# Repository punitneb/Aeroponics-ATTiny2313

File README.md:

# Aeroponics-ATTiny2313
This project is specifically tailored to components available in the Indian market, keeping in mind rural farm practices and conditions. At the same time attempting to keep the design suitable for urban farming.

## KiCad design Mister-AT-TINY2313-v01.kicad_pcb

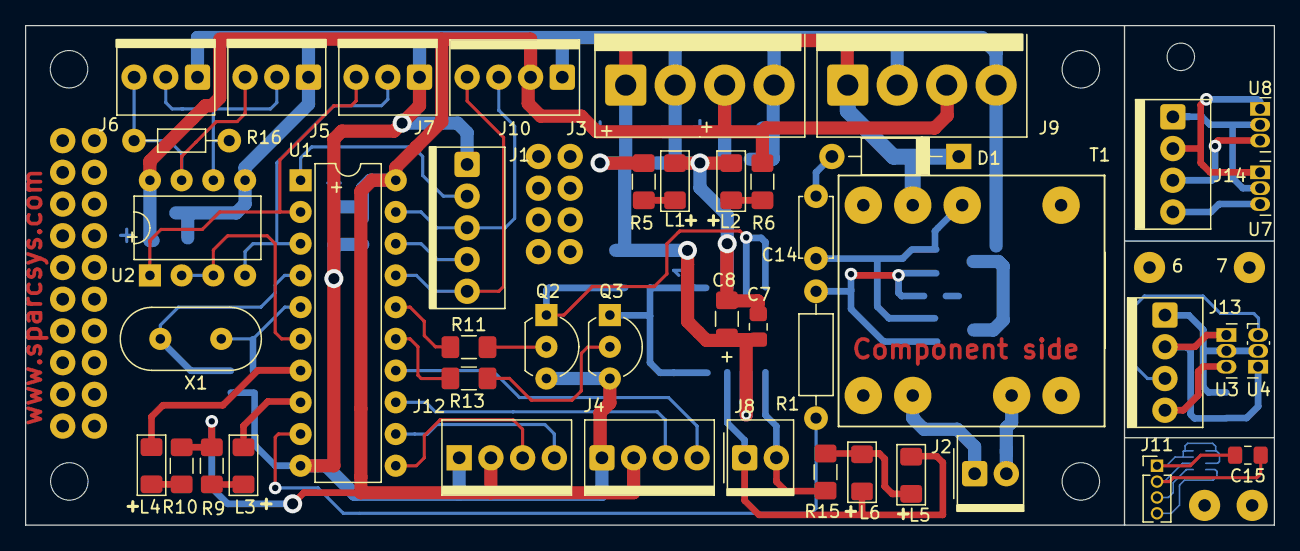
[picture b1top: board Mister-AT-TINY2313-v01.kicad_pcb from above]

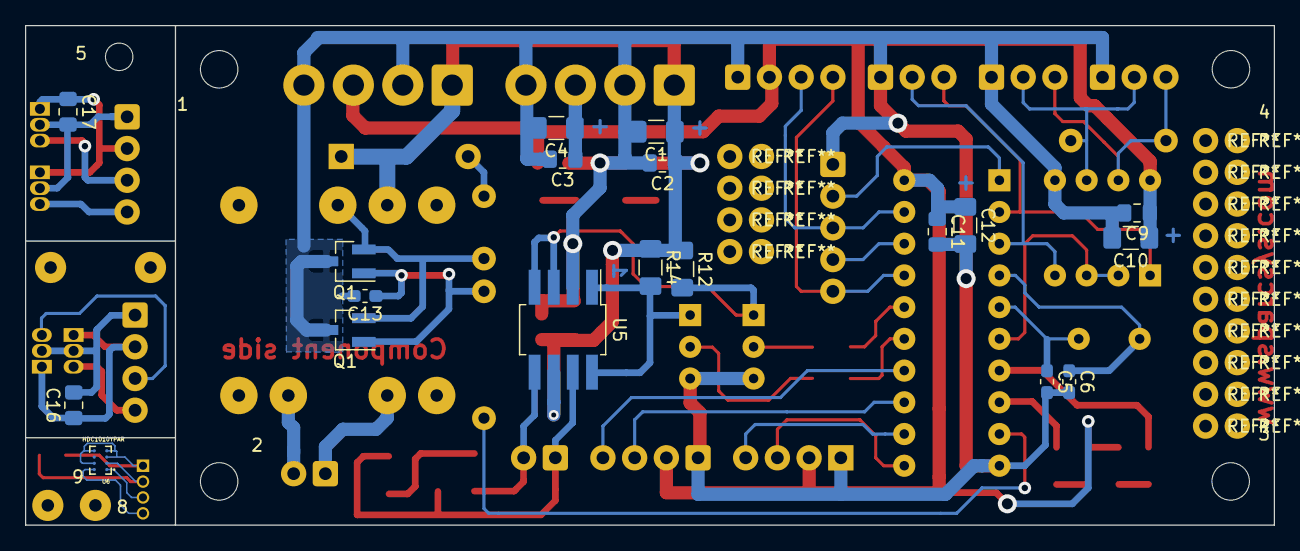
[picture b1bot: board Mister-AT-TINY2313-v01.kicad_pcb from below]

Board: 2 copper layers, 100.0 x 40.0 mm, 72 parts (19 on the bottom side), 51 nets.

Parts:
1, 2, 3, 4: MountingHole_3mm
5: MountingHole_2.2mm_M2
6, 7, 8, 9: SolderWirePad_1x01_Drill1mm
C1, C4, C8, C10, C12: 100uf/16V; C_1206_3216Metric_Pad1.42x1.75mm_HandSolder
C2, C3, C7, C9, C11: 104; C_0805_2012Metric_Pad1.15x1.40mm_HandSolder
C5, C6, C13: 22pf; C_0603_1608Metric_Pad1.05x0.95mm_HandSolder
C14: 0.22/100V; C_Disc_D4.7mm_W2.5mm_P5.00mm
C15, C16, C17: 104; R_0805_2012Metric_Pad1.15x1.40mm_HandSolder
D1: 1N4001; D_DO-41_SOD81_P10.16mm_Horizontal
J1: 5P RELI M; Molex_KK-254_AE-6410-05A_1x05_P2.54mm_Vertical
J2, J8: 2P RELI M; Molex_KK-254_AE-6410-02A_1x02_P2.54mm_Vertical
J3, J9: 4P CPU M; Hirose_DF63-4P-3.96DSA_1x04_P3.96mm_Horizontal
J4, J10, J12, J13, J14: 4P RELI M; Molex_KK-254_AE-6410-04A_1x04_P2.54mm_Vertical
J5, J6, J7: 3P RELI M; Molex_KK-254_AE-6410-03A_1x03_P2.54mm_Vertical
J11: 4P RELI M; PinHeader_1x04_P1.27mm_Vertical
L1: Green; LED_1206_3216Metric_Pad1.42x1.75mm_HandSolder
L2: Red; LED_1206_3216Metric_Pad1.42x1.75mm_HandSolder
L3: Blue; LED_1206_3216Metric_Pad1.42x1.75mm_HandSolder
L4: White; LED_1206_3216Metric_Pad1.42x1.75mm_HandSolder
L5: RED; LED_1206_3216Metric_Pad1.42x1.75mm_HandSolder
L6: BLUE; LED_1206_3216Metric_Pad1.42x1.75mm_HandSolder
Q1, Q1#2: TIP122; SOT-23_Handsoldering
Q2, Q3: BC547; TO-92L_Inline_Wide
R1: 10K; R_Axial_DIN0207_L6.3mm_D2.5mm_P10.16mm_Horizontal
R5, R6, R11, R12, R13, R14: 4K7; R_1206_3216Metric_Pad1.42x1.75mm_HandSolder
R9, R10, R15: 2K2; R_1206_3216Metric_Pad1.42x1.75mm_HandSolder
R16: 100E; R_Axial_DIN0204_L3.6mm_D1.6mm_P7.62mm_Horizontal
T1: Transformer-20x20-3.96mm-10p
U1: ATtiny2313-20PU; DIP-20_W7.62mm
U2: MAX485E; DIP-8_W7.62mm_Socket_LongPads
U3, U4, U7, U8: A1343; Allegro_SIP-3
U5: ZXMHC6A07T8-H-Bridge-FET; SOT-223-8
U6: HDC1010YPAR; BGA8C100X50P2X4_204X159X67N
X1: 11.0592MHz; Crystal_HC49-U_Vertical

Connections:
+5V: C3.1, C4.1, C9.1, C10.1, C11.1, C12.1, J3.3, J4.2, J9.3, J10.2, J12.2, R6.1, R9.1, R10.1, U1.20, U2.8
+12V: C1.1, C2.1, C7.1, C8.1, D1.1, J3.1, J9.1, R5.1, R12.1, R14.1, T1.4, U5.6
/GND_H20: C17.2, J14.1, U7.2, U8.2
/GND_HALL_VALVE: C16.2, J13.1, U3.2, U4.2
/GND_HUSENS: C15.2, J11.1, U6.B2, U6.C1, U6.D1, U6.D2
/HALL_H2O_LVL1: J14.3, U8.3
/HALL_H2O_LVL2: J14.4, U7.3
/HALL_VALVE_CLOSE: J13.4, U3.3
/HALL_VALVE_OPEN: J13.3, U4.3
/L1_Anode: L1.2, R5.2
/L2_Anode: L2.2, R6.2
/MISO: J1.4, U1.18
/MOSI: J1.5, J10.4, U1.17
/MOTOR+: J8.2, R15.1, U5.5
/MOTOR-: J8.1, L5.1, L6.2, U5.7
/MOTOR_LED: L5.2, L6.1, R15.2
/PIEZO1: J2.1, T1.7
/PIEZO2: J2.2, T1.8
/PORT_HALL_H2O_LVL1: J12.3, U1.11
/PORT_HALL_H2O_LVL2: J12.4, U1.12
/PORT_HALL_VALVE_CLOSE: J4.4, U1.14
/PORT_HALL_VALVE_OPEN: J4.3, U1.13
/PORT_LED_ACTIVITY: L4.1, U1.7
/PORT_LED_LOOP: L3.1, U1.8
/PORT_MOTOR_F: R11.2, U1.16
/PORT_MOTOR_R: R13.2, U1.15
/PORT_PWM: R1.2, U1.9
/PORT_RX: J7.3, U1.2, U2.1
/PORT_RX_EN: U1.6, U2.2, U2.3
/PORT_SCL: J1.3, J10.3, U1.19
/PORT_TX: J7.2, U1.3, U2.4
/PWMB: C13.1, Q1.1, Q1#2.1, R1.1
/PWMC: C14.2, Q1.2, Q1#2.2, T1.3
/Q2B_MOTOR_F: Q2.2, R11.1
/Q2C_MOTOR_F: Q2.1, R12.2, U5.3, U5.4
/Q3B_MOTOR_R: Q3.2, R13.1
/Q3C_MOTOR_R: Q3.1, R14.2, U5.1, U5.8
/RESET: J1.2, U1.1
/RS485+: J5.3, J6.3, R16.2, U2.7
/RS485-: J5.2, J6.2, R16.1, U2.6
/SCL_HSENSOR: J11.3, U6.A1
/SDA_HSENSOR: J11.4, U6.A2
/SNUB: C14.1, D1.2
/VCC_H20: C17.1, J14.2, U7.1, U8.1
/VCC_HALL_VALVE: C16.1, J13.2, U3.1, U4.1
/VCC_HUSENS: C15.1, J11.2, U6.B1
/XTAL1: C5.1, U1.5, X1.1
/XTAL2: C6.1, U1.4, X1.2
GND: C1.2, C2.2, C3.2, C4.2, C5.2, C6.2, C7.2, C8.2, C9.2, C10.2, C11.2, C12.2, C13.2, J1.1, J3.2, J3.4, J4.1, J5.1, J6.1, J7.1, J9.2, J9.4, J10.1, J12.1, L1.1, L2.1, Q1.3, Q1#2.3, Q2.3, Q3.3, U1.10, U2.5, U5.2
unnamed: L3.2, R9.2
unnamed: L4.2, R10.2
